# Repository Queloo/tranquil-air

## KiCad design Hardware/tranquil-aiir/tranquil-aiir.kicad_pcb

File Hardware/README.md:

# PROYECTO TRANQUIL-AIIR
Tranquil-aiir es un sistema de adquisición y visualización de señales cardíacas utilizando como base Raspberry Pi Pico.
## DESCRIPCIÓN
En el proyecto utilizamos un sensor AD8232 para capturar las señales eléctricas del corazón y una pantalla TFT ILI9488 para mostrar la señal ECG en tiempo real.
El objetivo de este trabajo es poder desarrollar un prototipo compacto y portátil para su uso sencillo y flexible.
## CARACTERÍSTICAS
- Captura de señal ECG mediante módulo AD8232.
- Procesamiento digital de la señal con Raspberry Pi Pico.
- Visualización en pantalla TFT ILI9341 de 320x480.
- Comunicación SPI entre microcontrolador y pantalla.
- Diseño de PCB personalizada.
- Alimentación mediante batería Li-Ion.

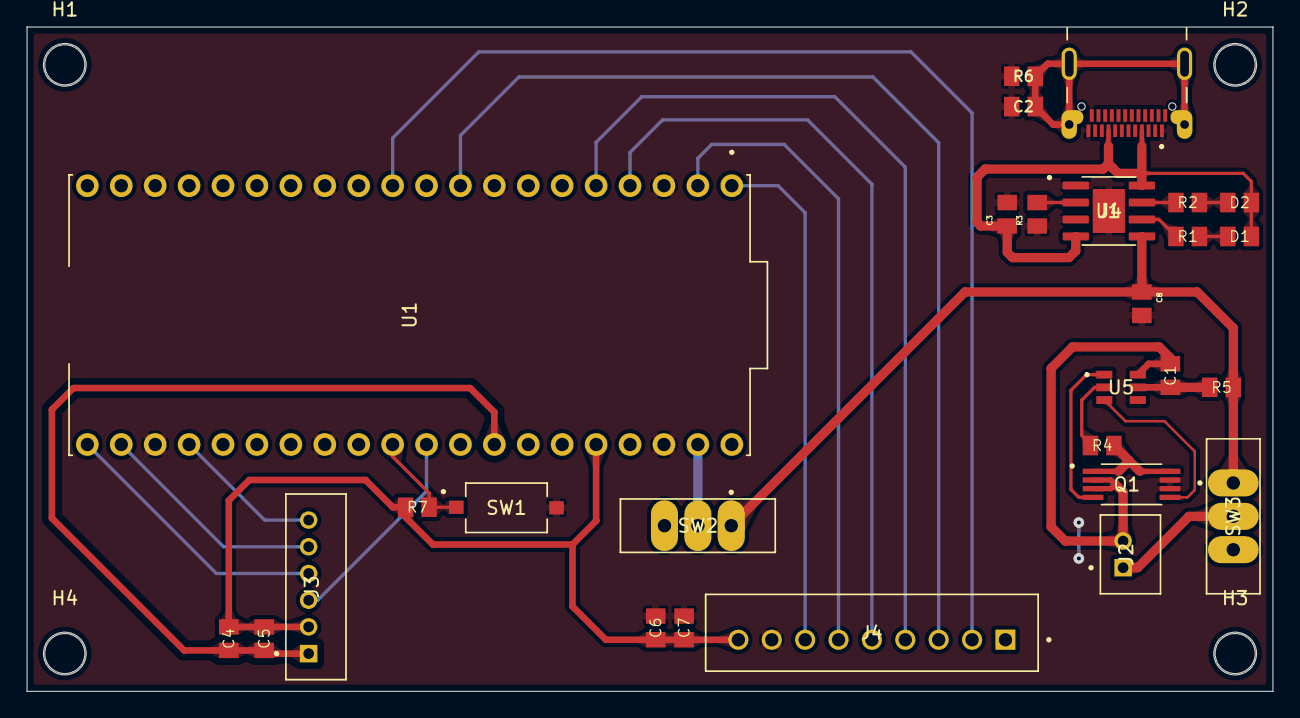
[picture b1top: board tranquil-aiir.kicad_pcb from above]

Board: 2 copper layers, 93.3 x 49.7 mm, 32 parts (0 on the bottom side), 30 nets.

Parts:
C1, C4, C6: 100nF 16V; CAPC2012X94N
C2: 4.7nF 50V-100V; CAPC2012X94N
C3, C5, C7, C8: 10uF 16V; CAPC2012X94N
D1, D2: LED; CAPC2012X94N
H1, H2, H3, H4: MountingHole; MountingHole_3.2mm_M3
J1: USB-C_CHARGER; TE_2345986-1
J2: BATTERY_18650; JST_B2B-PH-K-S
J3: SENSOR_AD8232_SOCKET; JST_B6B-PH-K
J4: Conn_01x09_Socket; JST_B9B-XH-A
Q1: FS8205A; SOP65P640X120-8N
R1, R2, R4: 1KΩ; CAPC2012X94N
R3: 1K5Ω; CAPC2012X94N
R5: 100Ω; CAPC2012X94N
R6: 1MΩ; CAPC2012X94N
R7: 10KΩ; CAPC2012X94N
SW1: SW_Push; SW_TS09-63-25-WT-160-SMT-TR
SW2, SW3: SW_SPDT; SW_EG1218
U1: RASPBERRY-PI-PICO; MODULE_SC0917
U4: TP4056; SOP127P600X175-9N
U5: DW01A; SOT95P280X145-6N

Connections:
+3V3: C4.1, C5.1, C6.1, C7.1, J3.2, J4.9, R7.1, U1.36 (3V3_OUT)
+5V: C3.1, D1.2 (A), D2.2 (A), J1.A4 (VBUS_A), J1.A9 (VBUS_A), J1.B4 (VBUS_B), J1.B9 (VBUS_B), U4.4 (VCC), U4.8 (CE)
+BATT: C8.1, R5.2, SW2.1 (A), SW3.1 (A), U4.5 (BAT)
-BATT: C1.2, J2.2, Q1.2, Q1.3, U5.6 (GND)
/ADC_OUTPUT: J3.3, U1.31 (GP26)
/CS_DISPLAY: J4.7, U1.1 (GP0)
/DC/RS_DISPLAY: J4.5, U1.4 (GP2)
/LED_DISPLAY: J4.2, U1.11 (GP8)
/LO+: J3.5, U1.22 (GP17)
/LO-: J3.4, U1.21 (GP16)
/MOSI_DISPLAY: J4.4, U1.5 (GP3)
/RESET_DISPLAY: J4.6, U1.2 (GP1)
/SCK_DISPLAY: J4.3, U1.9 (GP6)
/SHOTDOWN_SDN: J3.6, U1.24 (GP18)
GND: C2.2, C3.2, C6.2, C7.2, C8.2, J1.A1 (GND_A), J1.A12 (GND_A), J1.B1 (GND_B), J1.B12 (GND_B), J4.8, Q1.6, Q1.7, R3.1, R6.2, SW1.2, U1.3 (GND), U1.8 (GND), U1.13 (GND), U1.18 (GND), U1.23 (GND), U1.28 (GND), U1.38 (GND), U4.1 (TEMP), U4.3 (GND), U4.9 (EP)
GNDA: C4.2, C5.2, J3.1, U1.33 (AGND)
unnamed: C2.1, J1.SH1 (SHIELD), J1.SH2 (SHIELD), J1.SH3 (SHIELD), J1.SH4 (SHIELD), R6.1
unnamed: D1.1 (K), R1.2
unnamed: D2.1 (K), R2.2
unnamed: J2.1, SW3.2 (B)
unnamed: Q1.1, Q1.8, R4.1
unnamed: SW2.2 (B), U1.39 (VSYS)
unnamed: R7.2, SW1.1, U1.30 (~RUN)
unnamed: R3.2, U4.2 (PROG)
unnamed: R2.1, U4.7 (~CHRG)
unnamed: R1.1, U4.6 (~STDBY)
unnamed: R4.2, U5.2 (CS)
unnamed: Q1.5, U5.3 (OC)
unnamed: Q1.4, U5.1 (OD)
unnamed: C1.1, R5.1, U5.5 (VCC)
